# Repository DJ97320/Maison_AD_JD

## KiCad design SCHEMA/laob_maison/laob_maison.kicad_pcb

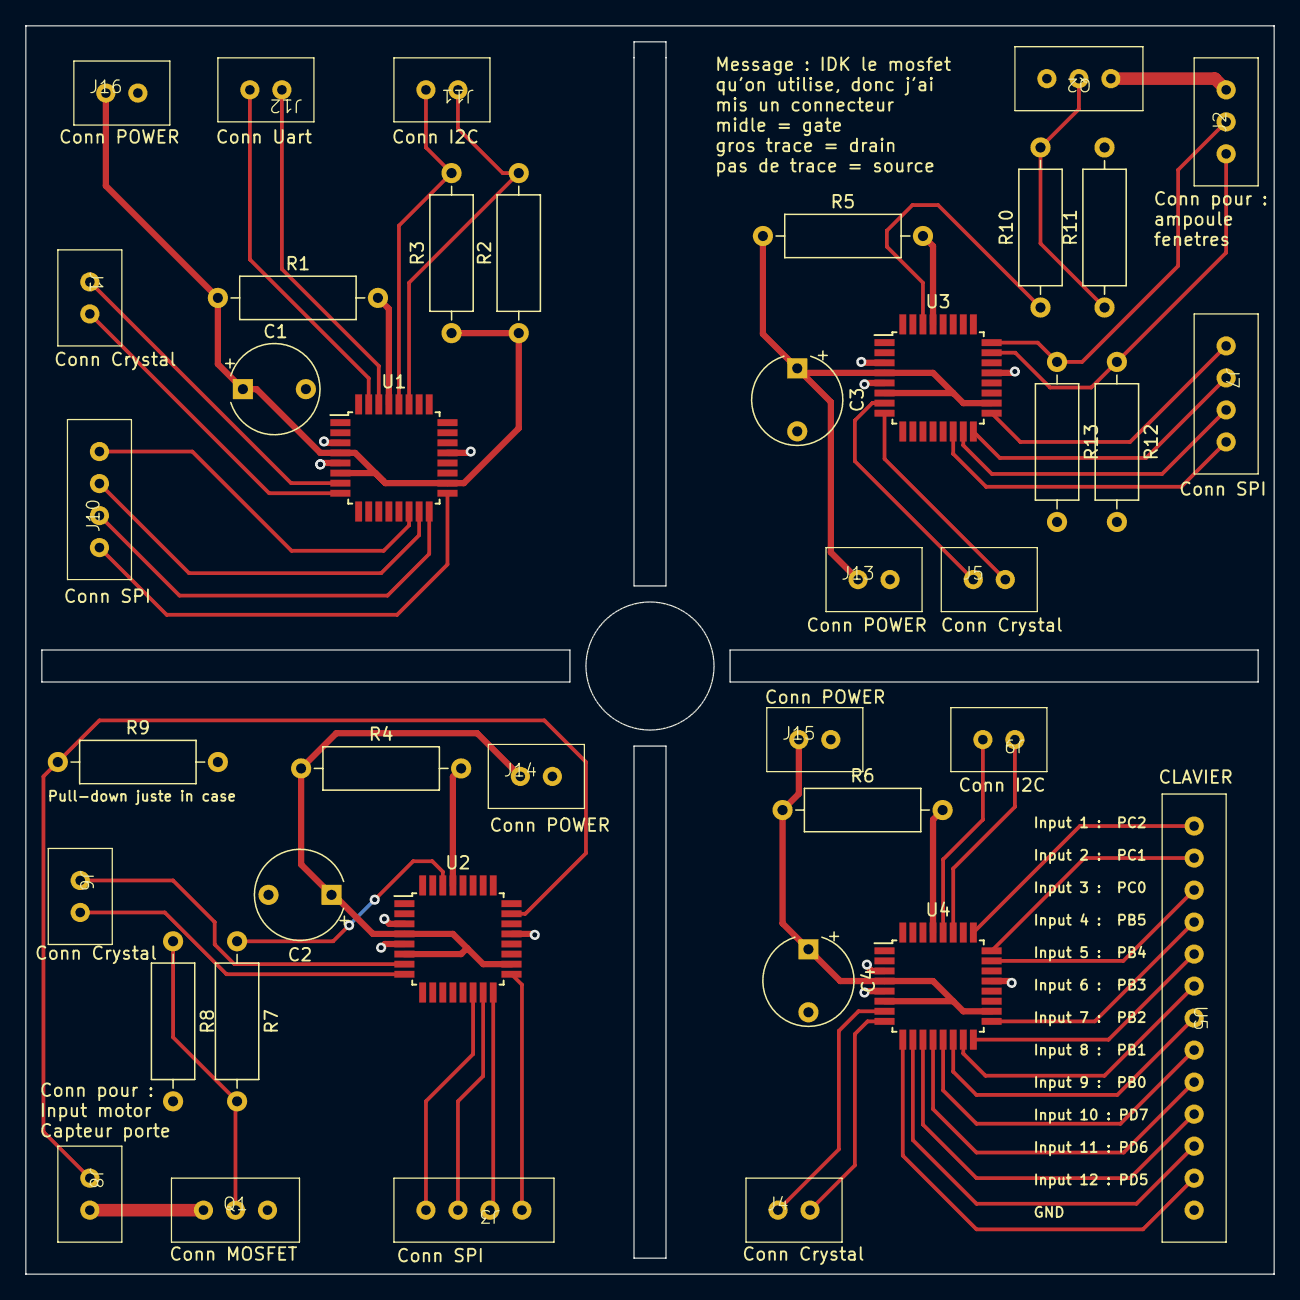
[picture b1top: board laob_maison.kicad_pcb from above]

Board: 2 copper layers, 99.1 x 99.1 mm, 40 parts (0 on the bottom side), 56 nets.

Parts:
C1, C2, C3, C4: 100nF; CP_Radial_Tantal_D7.0mm_P5.00mm
J1, J4, J5, J6: Conn_crystal; Conn1x2
J2: Conn_01x03; Conn1x3
J3, J7, J10: Conn_SPI; conn_1x4
J8: Conn_01x02; Conn1x2
J9, J11: Conn_I2C; Conn1x2
J12: Conn_Uart; Conn1x2
J13, J14, J15, J16: Conn_power; Conn1x2
Q1: NMOS_pour_porte; Conn1x3
Q2: NMOS_pour_ampoule; Conn1x3
R1, R4, R5, R6: 10k; R_Axial_DIN0309_L9.0mm_D3.2mm_P12.70mm_Horizontal
R2, R3, R9, R12, R13: 5k; R_Axial_DIN0309_L9.0mm_D3.2mm_P12.70mm_Horizontal
R7, R10: 1k; R_Axial_DIN0309_L9.0mm_D3.2mm_P12.70mm_Horizontal
R8, R11: 100k; R_Axial_DIN0309_L9.0mm_D3.2mm_P12.70mm_Horizontal
U1, U2, U3, U4: ATmega8A-A; TQFP-32_7x7mm_P0.8mm
U5: Clavier; Conn1x13_clavier

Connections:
/+5V: C1.1, J16.1, R1.1, R2.1, R3.1, U1.4 (VCC), U1.6 (VCC), U1.18 (AVCC)
/Moteur_capteur/+5V: C2.1, J14.1, R4.1, U2.4 (VCC), U2.6 (VCC), U2.18 (AVCC)
/clavier/+5V: C4.1, J15.1, R6.1, U4.4 (VCC), U4.6 (VCC), U4.18 (AVCC)
/clavier/Input_1: U4.25 (PC2), U5.1
/clavier/Input_2: U4.24 (PC1), U5.2
/clavier/Input_3: U4.23 (PC0), U5.3
/clavier/Input_4: U4.17 (PB5), U5.4
/clavier/Input_5: U4.16 (PB4), U5.5
/clavier/Input_6: U4.15 (PB3), U5.6
/clavier/Input_7: U4.14 (PB2), U5.7
/clavier/Input_8: U4.13 (PB1), U5.8
/clavier/Input_9: U4.12 (PB0), U5.9
/clavier/Input_10: U4.11 (PD7), U5.10
/clavier/Input_11: U4.10 (PD6), U5.11
/clavier/Input_12: U4.9 (PD5), U5.12
/fenetre_ampoule/+5V: C3.1, J13.1, R5.1, U3.4 (VCC), U3.6 (VCC), U3.18 (AVCC)
GND: C1.2, C2.2, C3.2, C4.2, J13.2, J14.2, J15.2, J16.2, Q1.3 (S), Q2.3 (S), R8.2, R9.2, R11.2, R12.2, R13.2, U1.3 (GND), U1.5 (GND), U1.21 (AGND), U2.3 (GND), U2.5 (GND), U2.21 (AGND), U3.3 (GND), U3.5 (GND), U3.21 (AGND), U4.3 (GND), U4.5 (GND), U4.21 (AGND), U5.13 (Com)
unnamed: J1.1, U1.7 (PB6/XTAL1)
unnamed: J1.2, U1.8 (PB7/XTAL2)
unnamed: J2.1, R12.1, U3.23 (PC0)
unnamed: J2.2, R13.1, U3.24 (PC1)
unnamed: J2.3, Q2.1 (D)
unnamed: J3.1, U2.14 (PB2)
unnamed: J3.2, U2.15 (PB3)
unnamed: J3.3, U2.16 (PB4)
unnamed: J3.4, U2.17 (PB5)
unnamed: J4.1, U4.7 (PB6/XTAL1)
unnamed: J4.2, U4.8 (PB7/XTAL2)
unnamed: J5.1, U3.7 (PB6/XTAL1)
unnamed: J5.2, U3.8 (PB7/XTAL2)
unnamed: J6.1, U2.7 (PB6/XTAL1)
unnamed: J6.2, U2.8 (PB7/XTAL2)
unnamed: J7.1, U3.14 (PB2)
unnamed: J7.2, U3.15 (PB3)
unnamed: J7.3, U3.16 (PB4)
unnamed: J7.4, U3.17 (PB5)
unnamed: J8.1, R9.1, U2.23 (PC0)
unnamed: J8.2, Q1.1 (D)
unnamed: J9.1, U4.27 (PC4)
unnamed: J9.2, U4.28 (PC5)
unnamed: J10.1, U1.14 (PB2)
unnamed: J10.2, U1.15 (PB3)
unnamed: J10.3, U1.16 (PB4)
unnamed: J10.4, U1.17 (PB5)
unnamed: J11.1, R2.2, U1.27 (PC4)
unnamed: J11.2, R3.2, U1.28 (PC5)
unnamed: J12.1, U1.30 (PD0)
unnamed: J12.2, U1.31 (PD1)
unnamed: Q1.2 (G), R7.2, R8.1
unnamed: Q2.2 (G), R10.2, R11.1
unnamed: R1.2, U1.29 (PC6/~RESET)
unnamed: R4.2, U2.29 (PC6/~RESET)
unnamed: R7.1, U2.30 (PD0)
unnamed: R5.2, U3.29 (PC6/~RESET)
unnamed: R10.1, U3.30 (PD0)
unnamed: R6.2, U4.29 (PC6/~RESET)

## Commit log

2023-12-07 SPI / I2C
2023-12-07 UART pour 8A
2023-12-10 Kicad Schema + PCB
